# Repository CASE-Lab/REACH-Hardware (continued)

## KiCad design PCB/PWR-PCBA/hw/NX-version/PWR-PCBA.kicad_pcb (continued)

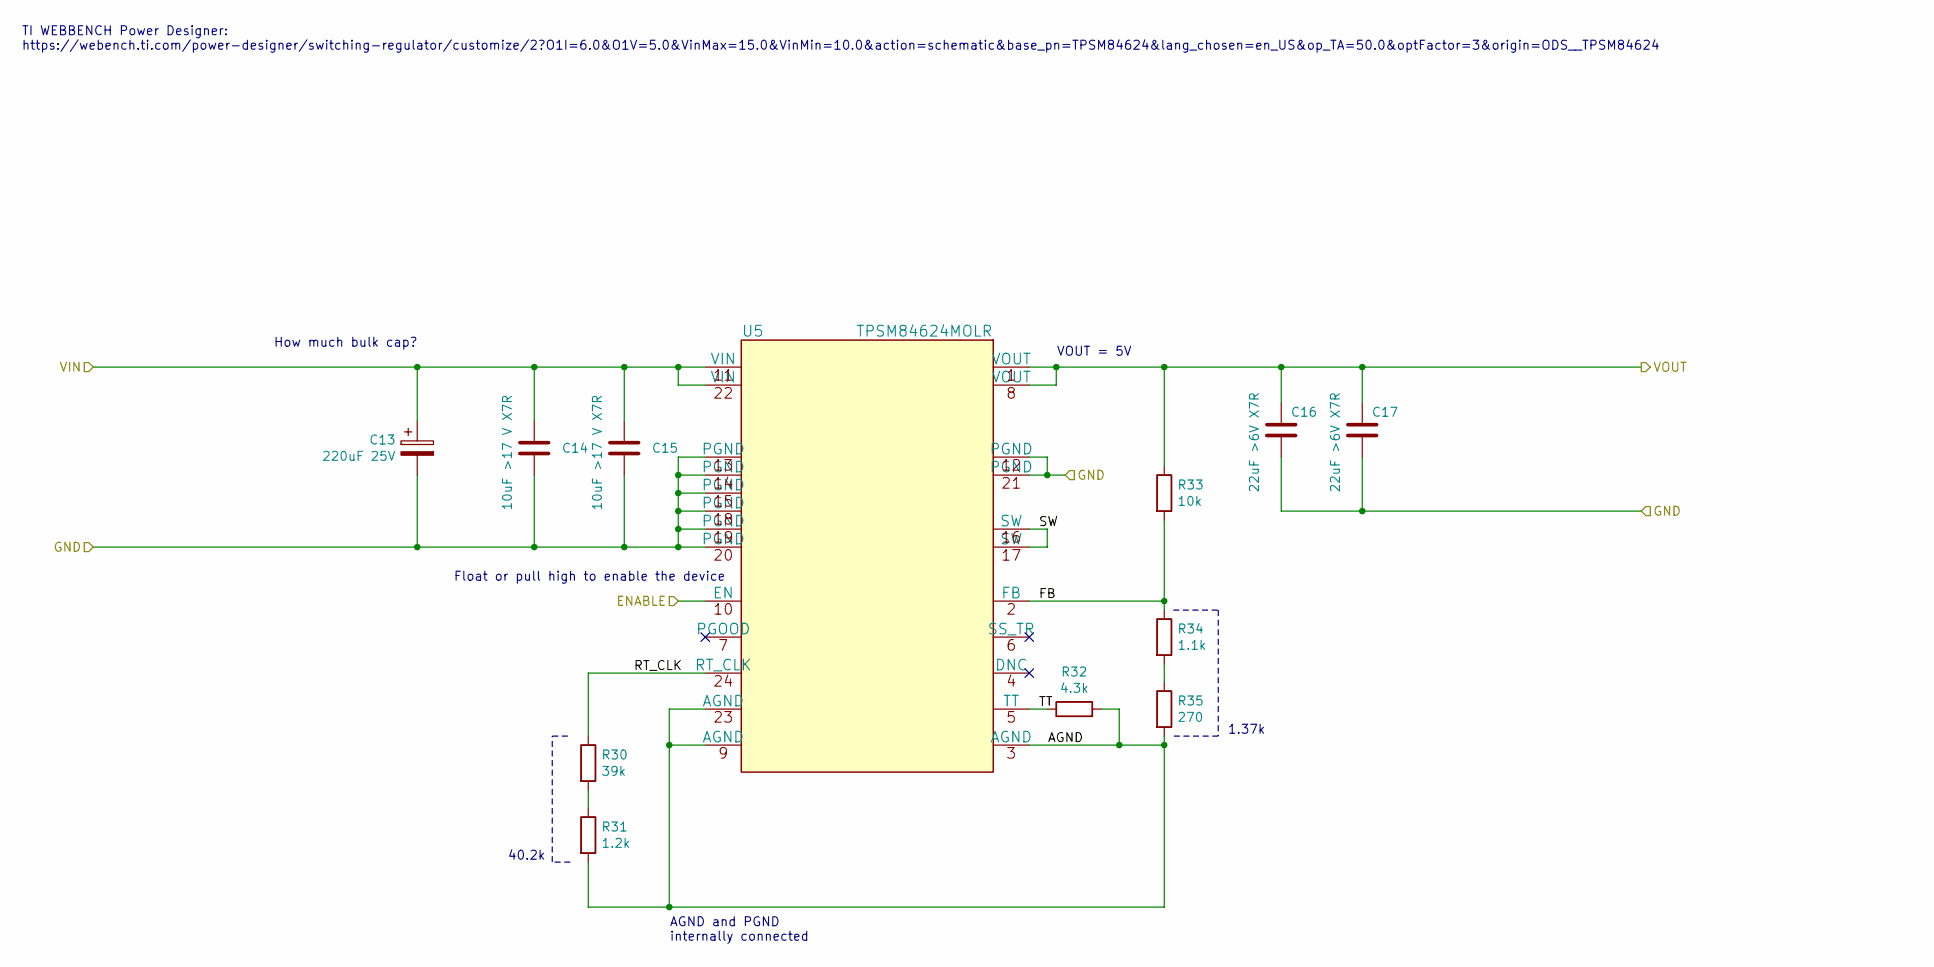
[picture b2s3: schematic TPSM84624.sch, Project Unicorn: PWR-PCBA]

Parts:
C13: 220uF 25V; CP_Radial_D8.0mm_P3.50mm; MPN ESE227M025AG3AA
C14, C15: 10uF >17 V X7R; C_0805_2012Metric; MPN TMK212BBJ106MG-T
C16, C17: 22uF >6V X7R; C_0805_2012Metric; MPN C0805C226M9PACTU
R30: 39k; R_0603_1608Metric
R31: 1.2k; R_0603_1608Metric
R32: 4.3k; R_0603_1608Metric
R33: 10k; R_0603_1608Metric
R34: 1.1k; R_0603_1608Metric
R35: 270; R_0603_1608Metric
U5: TPSM84624MOLR; MPN TPSM84624MOLR

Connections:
+5V: C16.1, C17.1, R33.1, U5.1 (VOUT), U5.8 (VOUT); also elsewhere on the board
+12V: C13.1, C14.1, C15.1, U5.11 (VIN), U5.22 (VIN); also elsewhere on the board
/5V DC/DC TPSM84624 /AGND: R31.2, R32.2, R35.2, U5.3 (AGND), U5.9 (AGND), U5.23 (AGND)
/5V DC/DC TPSM84624 /ENABLE: U5.10 (EN); also elsewhere on the board
/5V DC/DC TPSM84624 /FB: R33.2, R34.1, U5.2 (FB)
/5V DC/DC TPSM84624 /RT_CLK: R30.1, U5.24 (RT_CLK)
/5V DC/DC TPSM84624 /SW: U5.16 (SW), U5.17 (SW)
/5V DC/DC TPSM84624 /TT: R32.1, U5.5 (TT)
GND: C13.2, C14.2, C15.2, C16.2, C17.2, U5.12 (PGND), U5.13 (PGND), U5.14 (PGND), U5.15 (PGND), U5.18 (PGND), U5.19 (PGND), U5.20 (PGND), U5.21 (PGND); also elsewhere on the board
unnamed: R30.2, R31.1
unnamed: R34.2, R35.1

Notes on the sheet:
TI WEBBENCH Power Designer: https://webench.ti.com/power-designer/switching-regulator/customize/2?O1I=6.0&O1V=5.0&VinMax=15.0&VinMin=10.0&action=schematic&base_pn=TPSM84624&lang_chosen=en_US&op_TA=50.0&optFactor=3&origin=ODS__TPSM84624
1.37k
VOUT = 5V
AGND and PGND internally connected
40.2k
How much bulk cap?
Float or pull high to enable the device

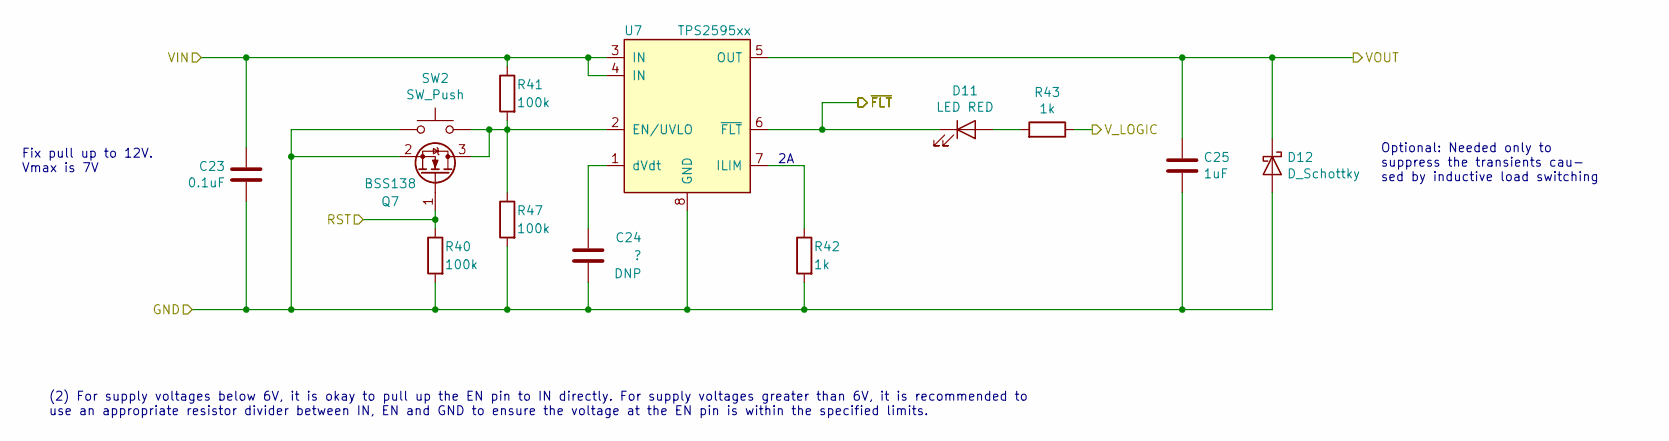
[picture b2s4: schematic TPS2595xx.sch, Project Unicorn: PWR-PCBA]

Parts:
C23: 0.1uF; C_0603_1608Metric
C24: ?; C_0603_1608Metric
C25: 1uF; C_0603_1608Metric
D11: LED RED; LED_0603_1608Metric
D12: D_Schottky; D_SOD-123; MPN 1N5819HW
Q7: BSS138; SOT-23
R40, R41, R47: 100k; R_0603_1608Metric
R42, R43: 1k; R_0603_1608Metric
SW2: SW_Push; KMR621NGLFS; MPN KMR621NGLFS
U7: TPS2595xx; WSON-8-1EP_2x2mm_P0.5mm_EP0.9x1.6mm_ThermalVias; MPN TPS259570DSGR

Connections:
+3V3: R43.1; also elsewhere on the board
+12V: C23.1, R41.1, U7.3 (IN), U7.4 (IN); also elsewhere on the board
/12V_FUSED: C25.1, D12.1 (K), U7.5 (OUT); also elsewhere on the board
/eF_12V_RST: Q7.1 (G), R40.1; also elsewhere on the board
/eF_12V_~FLT: D11.1 (K), U7.6 (~FLT); also elsewhere on the board
GND: C23.2, C24.2, C25.2, D12.2 (A), Q7.2 (S), R40.2, R42.2, R47.2, SW2.1, U7.8 (GND); also elsewhere on the board
unnamed: C24.1, U7.1 (dVdt)
unnamed: D11.2 (A), R43.2
unnamed: Q7.3 (D), R41.2, R47.1, SW2.2, U7.2 (EN/UVLO)
unnamed: R42.1, U7.7 (ILIM)

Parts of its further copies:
C18: 0.1uF; C_0603_1608Metric
C19: ?; C_0603_1608Metric
C20: 1uF; C_0603_1608Metric
D9: LED RED; LED_0603_1608Metric
D10: D_Schottky; D_SOD-123; MPN 1N5819HW
Q6: BSS138; SOT-23
R36, R37, R46: 100k; R_0603_1608Metric
R38, R39: 1k; R_0603_1608Metric
SW1: SW_Push; KMR621NGLFS; MPN KMR621NGLFS
U6: TPS2595xx; WSON-8-1EP_2x2mm_P0.5mm_EP0.9x1.6mm_ThermalVias; MPN TPS259570DSGR

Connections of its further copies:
+3V3: R39.1; also elsewhere on the board
+5V: C18.1, R37.1, U6.3 (IN), U6.4 (IN); also elsewhere on the board
/5V_FUSED: C20.1, D10.1 (K), U6.5 (OUT); also elsewhere on the board
/eF_5V_RST: Q6.1 (G), R36.1; also elsewhere on the board
/eF_5V_~FLT: D9.1 (K), U6.6 (~FLT); also elsewhere on the board
GND: C18.2, C19.2, C20.2, D10.2 (A), Q6.2 (S), R36.2, R38.2, R46.2, SW1.1, U6.8 (GND); also elsewhere on the board
unnamed: C19.1, U6.1 (dVdt)
unnamed: D9.2 (A), R39.2
unnamed: Q6.3 (D), R37.2, R46.1, SW1.2, U6.2 (EN/UVLO)
unnamed: R38.1, U6.7 (ILIM)

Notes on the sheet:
Optional: Needed only to suppress the transients cau- sed by inductive load switching
Fix pull up to 12V. Vmax is 7V
(2) For supply voltages below 6V, it is okay to pull up the EN pin to IN directly. For supply voltages greater than 6V, it is recommended to use an appropriate resistor divider between IN, EN and GND to ensure the voltage at the EN pin is within the specified limits.

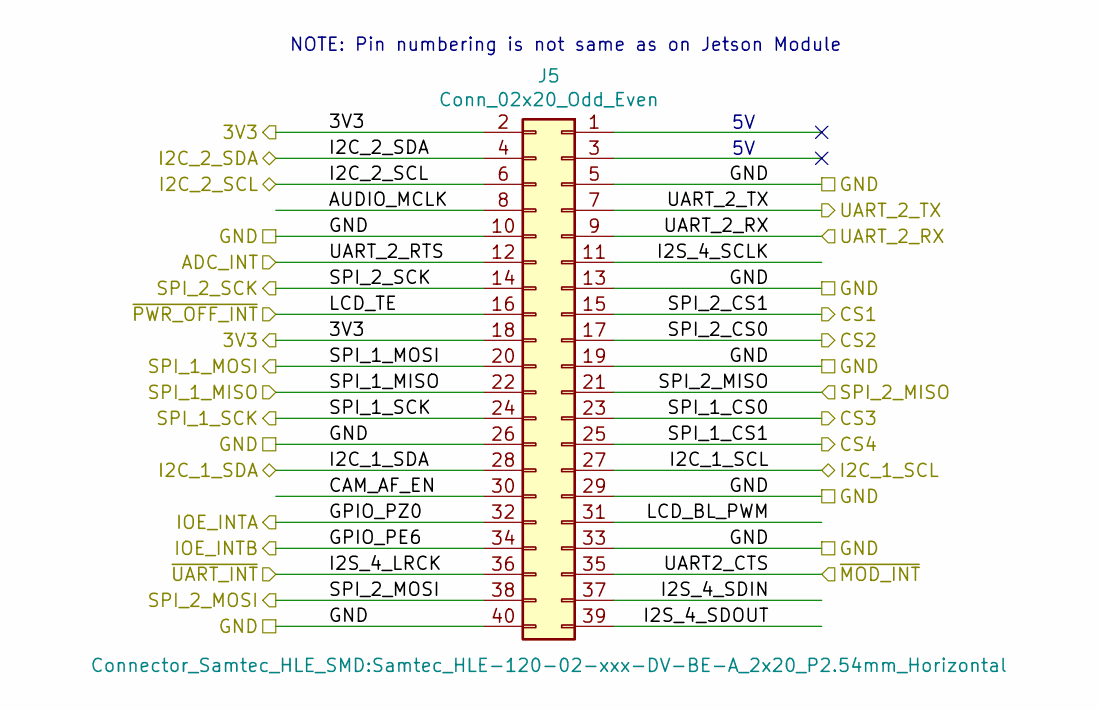
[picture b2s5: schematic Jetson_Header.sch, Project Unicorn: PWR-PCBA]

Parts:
J5: Conn_02x20_Odd_Even; Samtec_HLE-120-02-xxx-DV-BE-A_2x20_P2.54mm_Horizontal; MPN HLE-120-02-F-DV-BE-A

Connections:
+3V3: J5.2, J5.18; also elsewhere on the board
/ADC_INT: J5.12; also elsewhere on the board
/I2C_INT_SCL: J5.6; also elsewhere on the board
/I2C_INT_SDA: J5.4; also elsewhere on the board
/Jetson Header/AUDIO_MCLK: J5.8
/Jetson Header/CAM_AF_EN: J5.30
/Jetson Header/I2C_1_SCL: J5.27; also elsewhere on the board
/Jetson Header/I2C_1_SDA: J5.28; also elsewhere on the board
/Jetson Header/I2S_4_SCLK: J5.11
/Jetson Header/I2S_4_SDIN: J5.37
/Jetson Header/I2S_4_SDOUT: J5.39
/Jetson Header/IOE_INTA: J5.32
/Jetson Header/IOE_INTB: J5.34
/Jetson Header/LCD_BL_PWM: J5.31
/Jetson Header/SPI_1_MISO: J5.22; also elsewhere on the board
/Jetson Header/SPI_1_MOSI: J5.20; also elsewhere on the board
/Jetson Header/SPI_1_SCK: J5.24; also elsewhere on the board
/Jetson Header/SPI_2_MISO: J5.21; also elsewhere on the board
/Jetson Header/SPI_2_MOSI: J5.38; also elsewhere on the board
/Jetson Header/SPI_2_SCK: J5.14; also elsewhere on the board
/Jetson Header/UART_2_RX: J5.9; also elsewhere on the board
/Jetson Header/UART_2_TX: J5.7; also elsewhere on the board
/Jetson Header/~MOD_INT: J5.35; also elsewhere on the board
/Jetson Header/~UART_INT: J5.36; also elsewhere on the board
/SPI_2_CS1: J5.15; also elsewhere on the board
/SPI_2_CS2: J5.17; also elsewhere on the board
/SPI_2_CS3: J5.23; also elsewhere on the board
/SPI_2_CS4: J5.25; also elsewhere on the board
/~PWR_OFF_INT: J5.16; also elsewhere on the board
GND: J5.5, J5.10, J5.13, J5.19, J5.26, J5.29, J5.33, J5.40; also elsewhere on the board

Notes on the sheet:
NOTE: Pin numbering is not same as on Jetson Module

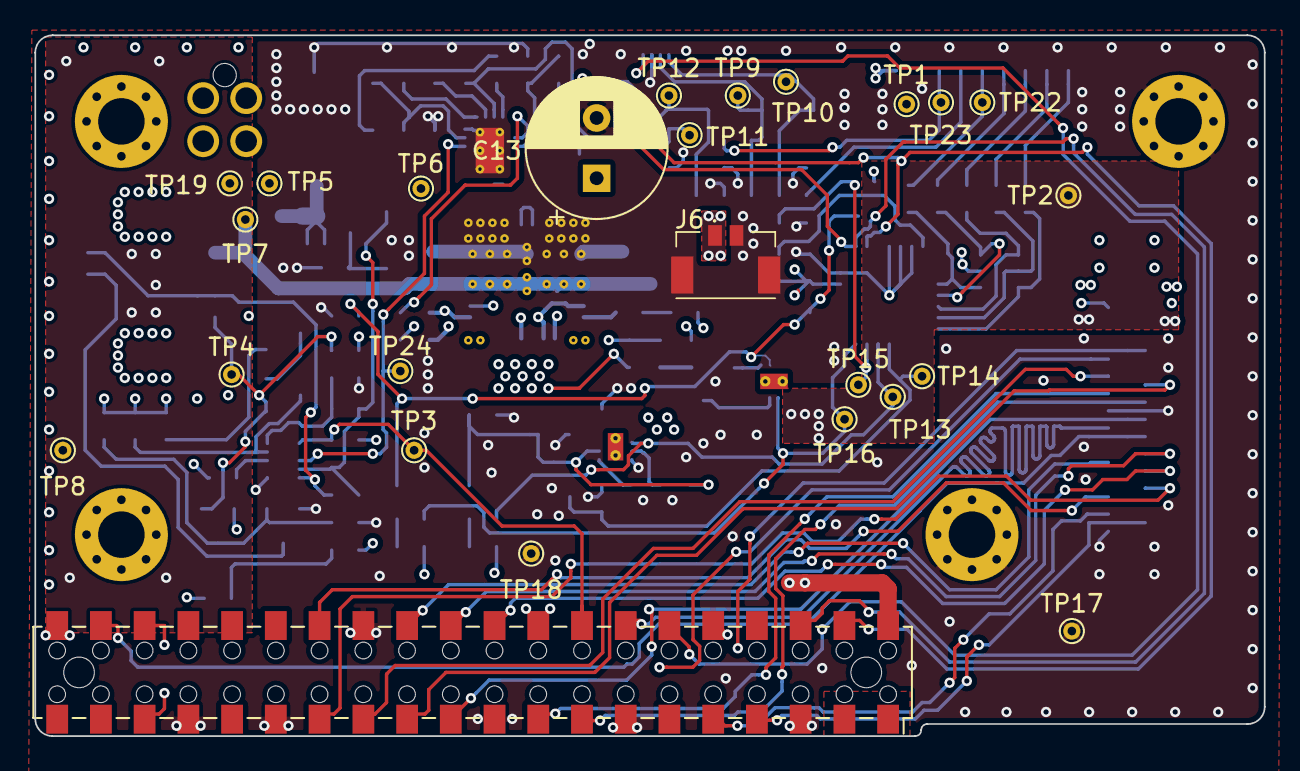
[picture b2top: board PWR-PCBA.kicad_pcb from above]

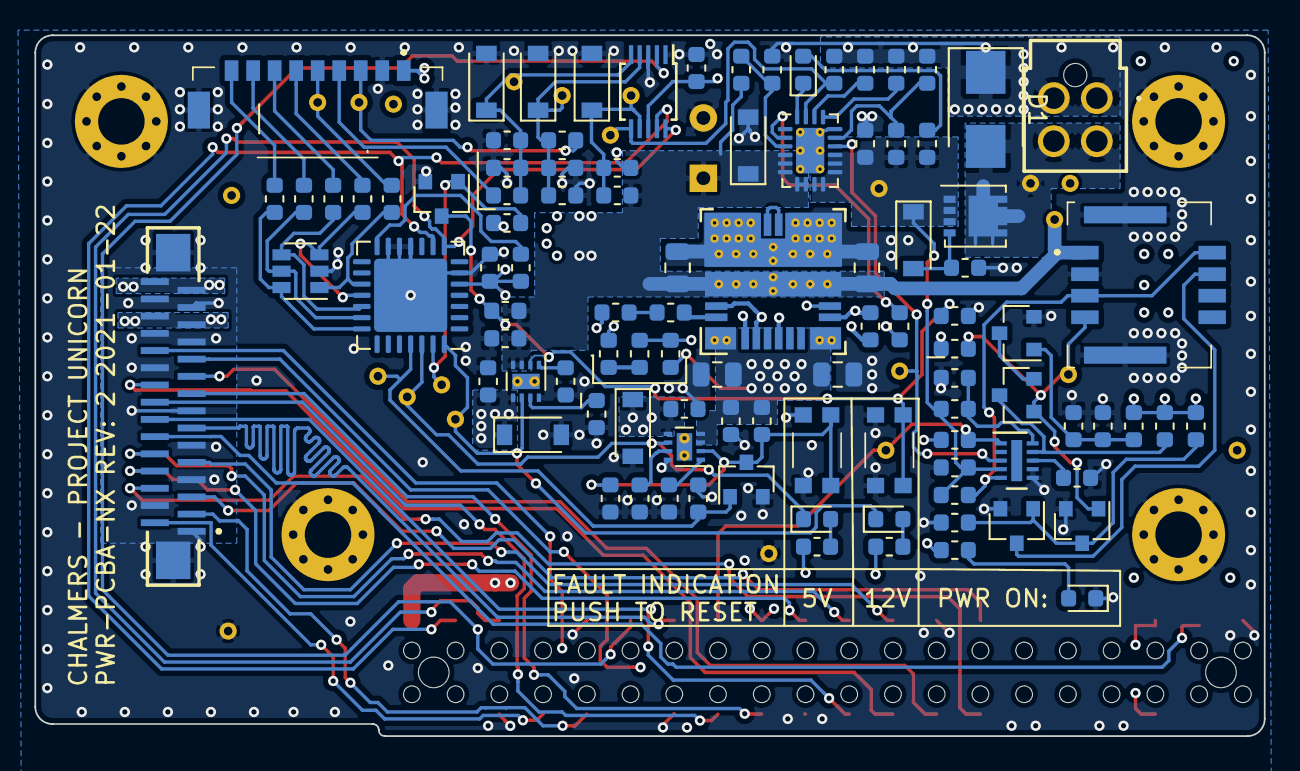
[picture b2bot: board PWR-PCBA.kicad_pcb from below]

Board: 4 copper layers, 71.4 x 40.7 mm, 129 parts (100 on the bottom side), 84 nets.

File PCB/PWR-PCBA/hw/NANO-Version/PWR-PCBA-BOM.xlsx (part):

Project Unicorn: PWR-PCBA BOM |  | Chalmers University of Technology
REV: 2 |  | REV Date: 2020-07-22
Reference | Qty | Value | Distributor | Distributor PN | MPN | Manufacturer | DNP | Comments
Non PCB Items
J1-CABLE | 1 | NanoFit 02x02 cable | Mouser | 538-105308-1204 | 1053081204 | Molex
Nano fit pre-crimped receptable | 2 | 300 mm double ended | Mouser | 538-79758-2140 | 79758-2140 | Molex |  | Buy terminals instead if crimp tool is accessible
J2-CABLE | 1 | MicroLock 02x04 cable | RS | 186-5275 | 505432-0801 | Molex
J4-CABLE | 1 | MicroLock 01x09 cable | Mouser | 538-204532-0901 | 2045320901 | Molex
MicroLock crimp receptable | 17 | Tin plated receptable | RS | 161-5947 | 505431-1000 | Molex |  | Buy crimped leads if no crimp tools is accesible
J5-CABLE | 1 | 30 pin samtec FFC 2" | RS | 197-6642 | FJH-30-D-02.00-4 | Samtec |  | Same side (D)
Kicad CSV Imported Items
C12 C13 | 2 | 220uF 25V | Elfa | 301-51-797 | ESE227M025AG3AA | KEMET
C14 C15 | 2 | 10uF >17 V X7R | RS | 184-3756 | TMK212BBJ106MG-T | Taiyo Yuden
C16 C17 | 2 | 22uF >6V X7R | RS | 691-1177 | C0805C226M9PACTU | Kemet
C2 C6 C1 C7 C8 C3 C10 C18 C23 | 9 | 0.1uF
C4 C5 C20 C25 | 4 | 1uF
C9 C19 C24 | 3 | ? |  |  |  |  | DNP
D1 | 1 | D_TVS | Mouser | 576-TPSMB20CA | TPSMB20CA | Littlefuse
D13 | 1 | LED GREEN
D2 | 1 | 12V | CASE |  | MMSZ5242B-G3-08 | Vishay
D3 D5 D4 | 3 | 5.1V | CASE |  | MMSZ5232B-7-F | Diodes Inc.
D6 | 1 | ESDA6V1-5SC6 | RS | 250-066 | ESDA6V1-5SC6 | ST
D7 D9 D11 | 3 | LED RED
D8 D10 D12 | 3 | D_Schottky | Mouser | 621-1N5819HW-F | 1N5819HW | Diodes Incorporated
H1 H3 H2 H4 | 4 | MountingHole_Pad
J1 | 1 | NanoFit 02x02 | Mouser | 538-105310-1204 | 105310-1204 | Molex
J2 | 1 | Micro Lock 02x04 | RS | 186-5193 | 5054330871 | Molex |  | Connetor for power on/off and LED indication
J3 | 1 | ZF5S-30-03-T-WT | Mouser | 200-ZF5S3003TWTTR | ZF5S-30-03-T-WT-TR | Samtec |  | To FP-PCBA
J4 | 1 | Micro Lock 01x09 | Elfa | 301-76-000 | 205957-0971 | Molex
J5 | 1 | Conn_02x20_Odd_Even | Mouser | 200-HLE12002FDVBEA | HLE-120-02-F-DV-BE-A | Samtec
Q1 | 1 | DMP3013SFV | Mouser | 621-DMP3013SFV-7 | DMP3013SFV-7 | Diodes Incorporated
Q2 Q4 Q5 Q3 Q6 Q7 | 6 | BSS138
R11 R23 | 2 | 1.6M
R13 R17 R15 | 3 | 27k
R2 | 1 | 1M
R22 R21 R20 R19 R18 | 5 | 160
R25 | 1 | 18k
R26 R30 | 2 | 39k
R27 | 1 | 2k
R28 | 1 | 270k
R29 | 1 | 30k
R31 | 1 | 1.2k
R32 | 1 | 4.3k
R33 | 1 | 10k
R34 | 1 | 1.1k
R35 | 1 | 270
R45 R38 R39 R42 R43 | 5 | 1k
R5 R3 R12 R4 R1 R10 R9 R16 R14 R6 R44 R24 R36 R37 R40 R41 | 16 | 100k
R7 | 1 | 0
R8 | 1 | ? |  |  |  |  | DNP
SW1 SW2 | 2 | SW_Push | CASE |  | KMR621NGLFS | C&K Components
TP1 TP2 TP3 TP4 TP21 TP20 TP19 TP18 TP17 TP16 TP15 TP14 TP13 TP12 TP11 TP10 TP9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 | 24 | TestPoint
U1 | 1 | MCP23017_ML | RS | 687-8773 | MCP23017-E/ML | Microchip
U2 | 1 | LTC2955xDDB-1 | RS | 884-6927 | LTC2955IDDB-1#TRMPBF | LT
U3 | 1 | ADS1015BQDGSRQ1 | Mouser | 595-ADS1015BQDGSRQ1 | ADS1015BQDGSRQ1 | TI
U4 | 1 | TPS25940x-Q1 | Mouser | 595-TPS25940LQRVCRQ1 | TPS25940LQRVCRQ1 | TI |  | Latching and automotive variant
U6 U7 | 2 | TPS2595xx | Mouser | 595-TPS259570DSGR | TPS259570DSGR | TI
0 | 0 | 0 | 0 | 0 | 0 | 0 | 0 | 0
0 | 0 | 0 | 0 | 0 | 0 | 0 | 0 | 0
0 | 0 | 0 | 0 | 0 | 0 | 0 | 0 | 0
0 | 0 | 0 | 0 | 0 | 0 | 0 | 0 | 0
0 | 0 | 0 | 0 | 0 | 0 | 0 | 0 | 0
0 | 0 | 0 | 0 | 0 | 0 | 0 | 0 | 0
0 | 0 | 0 | 0 | 0 | 0 | 0 | 0 | 0
0 | 0 | 0 | 0 | 0 | 0 | 0 | 0 | 0
0 | 0 | 0 | 0 | 0 | 0 | 0 | 0 | 0
0 | 0 | 0 | 0 | 0 | 0 | 0 | 0 | 0
0 | 0 | 0 | 0 | 0 | 0 | 0 | 0 | 0
0 | 0 | 0 | 0 | 0 | 0 | 0 | 0 | 0
0 | 0 | 0 | 0 | 0 | 0 | 0 | 0 | 0
0 | 0 | 0 | 0 | 0 | 0 | 0 | 0 | 0
0 | 0 | 0 | 0 | 0 | 0 | 0 | 0 | 0
0 | 0 | 0 | 0 | 0 | 0 | 0 | 0 | 0
0 | 0 | 0 | 0 | 0 | 0 | 0 | 0 | 0
0 | 0 | 0 | 0 | 0 | 0 | 0 | 0 | 0
0 | 0 | 0 | 0 | 0 | 0 | 0 | 0 | 0
0 | 0 | 0 | 0 | 0 | 0 | 0 | 0 | 0
0 | 0 | 0 | 0 | 0 | 0 | 0 | 0 | 0
0 | 0 | 0 | 0 | 0 | 0 | 0 | 0 | 0
0 | 0 | 0 | 0 | 0 | 0 | 0 | 0 | 0
0 | 0 | 0 | 0 | 0 | 0 | 0 | 0 | 0
0 | 0 | 0 | 0 | 0 | 0 | 0 | 0 | 0
0 | 0 | 0 | 0 | 0 | 0 | 0 | 0 | 0
0 | 0 | 0 | 0 | 0 | 0 | 0 | 0 | 0
0 | 0 | 0 | 0 | 0 | 0 | 0 | 0 | 0
0 | 0 | 0 | 0 | 0 | 0 | 0 | 0 | 0
0 | 0 | 0 | 0 | 0 | 0 | 0 | 0 | 0
0 | 0 | 0 | 0 | 0 | 0 | 0 | 0 | 0
0 | 0 | 0 | 0 | 0 | 0 | 0 | 0 | 0
0 | 0 | 0 | 0 | 0 | 0 | 0 | 0 | 0
0 | 0 | 0 | 0 | 0 | 0 | 0 | 0 | 0
0 | 0 | 0 | 0 | 0 | 0 | 0 | 0 | 0
0 | 0 | 0 | 0 | 0 | 0 | 0 | 0 | 0
0 | 0 | 0 | 0 | 0 | 0 | 0 | 0 | 0
0 | 0 | 0 | 0 | 0 | 0 | 0 | 0 | 0
0 | 0 | 0 | 0 | 0 | 0 | 0 | 0 | 0
0 | 0 | 0 | 0 | 0 | 0 | 0 | 0 | 0
0 | 0 | 0 | 0 | 0 | 0 | 0 | 0 | 0
0 | 0 | 0 | 0 | 0 | 0 | 0 | 0 | 0
0 | 0 | 0 | 0 | 0 | 0 | 0 | 0 | 0
0 | 0 | 0 | 0 | 0 | 0 | 0 | 0 | 0
0 | 0 | 0 | 0 | 0 | 0 | 0 | 0 | 0
0 | 0 | 0 | 0 | 0 | 0 | 0 | 0 | 0
0 | 0 | 0 | 0 | 0 | 0 | 0 | 0 | 0
0 | 0 | 0 | 0 | 0 | 0 | 0 | 0 | 0
0 | 0 | 0 | 0 | 0 | 0 | 0 | 0 | 0
0 | 0 | 0 | 0 | 0 | 0 | 0 | 0 | 0
0 | 0 | 0 | 0 | 0 | 0 | 0 | 0 | 0
0 | 0 | 0 | 0 | 0 | 0 | 0 | 0 | 0
0 | 0 | 0 | 0 | 0 | 0 | 0 | 0 | 0
0 | 0 | 0 | 0 | 0 | 0 | 0 | 0 | 0
0 | 0 | 0 | 0 | 0 | 0 | 0 | 0 | 0
0 | 0 | 0 | 0 | 0 | 0 | 0 | 0 | 0
0 | 0 | 0 | 0 | 0 | 0 | 0 | 0 | 0
0 | 0 | 0 | 0 | 0 | 0 | 0 | 0 | 0
0 | 0 | 0 | 0 | 0 | 0 | 0 | 0 | 0
0 | 0 | 0 | 0 | 0 | 0 | 0 | 0 | 0
0 | 0 | 0 | 0 | 0 | 0 | 0 | 0 | 0
0 | 0 | 0 | 0 | 0 | 0 | 0 | 0 | 0
0 | 0 | 0 | 0 | 0 | 0 | 0 | 0 | 0
0 | 0 | 0 | 0 | 0 | 0 | 0 | 0 | 0
0 | 0 | 0 | 0 | 0 | 0 | 0 | 0 | 0
0 | 0 | 0 | 0 | 0 | 0 | 0 | 0 | 0
0 | 0 | 0 | 0 | 0 | 0 | 0 | 0 | 0
0 | 0 | 0 | 0 | 0 | 0 | 0 | 0 | 0
0 | 0 | 0 | 0 | 0 | 0 | 0 | 0 | 0
0 | 0 | 0 | 0 | 0 | 0 | 0 | 0 | 0
0 | 0 | 0 | 0 | 0 | 0 | 0 | 0 | 0
0 | 0 | 0 | 0 | 0 | 0 | 0 | 0 | 0
0 | 0 | 0 | 0 | 0 | 0 | 0 | 0 | 0
0 | 0 | 0 | 0 | 0 | 0 | 0 | 0 | 0
0 | 0 | 0 | 0 | 0 | 0 | 0 | 0 | 0
0 | 0 | 0 | 0 | 0 | 0 | 0 | 0 | 0
0 | 0 | 0 | 0 | 0 | 0 | 0 | 0 | 0
0 | 0 | 0 | 0 | 0 | 0 | 0 | 0 | 0
0 | 0 | 0 | 0 | 0 | 0 | 0 | 0 | 0
0 | 0 | 0 | 0 | 0 | 0 | 0 | 0 | 0
0 | 0 | 0 | 0 | 0 | 0 | 0 | 0 | 0
0 | 0 | 0 | 0 | 0 | 0 | 0 | 0 | 0
0 | 0 | 0 | 0 | 0 | 0 | 0 | 0 | 0
0 | 0 | 0 | 0 | 0 | 0 | 0 | 0 | 0
0 | 0 | 0 | 0 | 0 | 0 | 0 | 0 | 0
0 | 0 | 0 | 0 | 0 | 0 | 0 | 0 | 0
0 | 0 | 0 | 0 | 0 | 0 | 0 | 0 | 0
0 | 0 | 0 | 0 | 0 | 0 | 0 | 0 | 0
0 | 0 | 0 | 0 | 0 | 0 | 0 | 0 | 0
0 | 0 | 0 | 0 | 0 | 0 | 0 | 0 | 0
0 | 0 | 0 | 0 | 0 | 0 | 0 | 0 | 0
0 | 0 | 0 | 0 | 0 | 0 | 0 | 0 | 0
0 | 0 | 0 | 0 | 0 | 0 | 0 | 0 | 0
0 | 0 | 0 | 0 | 0 | 0 | 0 | 0 | 0
0 | 0 | 0 | 0 | 0 | 0 | 0 | 0 | 0
0 | 0 | 0 | 0 | 0 | 0 | 0 | 0 | 0
0 | 0 | 0 | 0 | 0 | 0 | 0 | 0 | 0
0 | 0 | 0 | 0 | 0 | 0 | 0 | 0 | 0
0 | 0 | 0 | 0 | 0 | 0 | 0 | 0 | 0
0 | 0 | 0 | 0 | 0 | 0 | 0 | 0 | 0
0 | 0 | 0 | 0 | 0 | 0 | 0 | 0 | 0
0 | 0 | 0 | 0 | 0 | 0 | 0 | 0 | 0
0 | 0 | 0 | 0 | 0 | 0 | 0 | 0 | 0
0 | 0 | 0 | 0 | 0 | 0 | 0 | 0 | 0
0 | 0 | 0 | 0 | 0 | 0 | 0 | 0 | 0
0 | 0 | 0 | 0 | 0 | 0 | 0 | 0 | 0
0 | 0 | 0 | 0 | 0 | 0 | 0 | 0 | 0
0 | 0 | 0 | 0 | 0 | 0 | 0 | 0 | 0
0 | 0 | 0 | 0 | 0 | 0 | 0 | 0 | 0
0 | 0 | 0 | 0 | 0 | 0 | 0 | 0 | 0
0 | 0 | 0 | 0 | 0 | 0 | 0 | 0 | 0
0 | 0 | 0 | 0 | 0 | 0 | 0 | 0 | 0
0 | 0 | 0 | 0 | 0 | 0 | 0 | 0 | 0
0 | 0 | 0 | 0 | 0 | 0 | 0 | 0 | 0
0 | 0 | 0 | 0 | 0 | 0 | 0 | 0 | 0
0 | 0 | 0 | 0 | 0 | 0 | 0 | 0 | 0
0 | 0 | 0 | 0 | 0 | 0 | 0 | 0 | 0
0 | 0 | 0 | 0 | 0 | 0 | 0 | 0 | 0
0 | 0 | 0 | 0 | 0 | 0 | 0 | 0 | 0
0 | 0 | 0 | 0 | 0 | 0 | 0 | 0 | 0
0 | 0 | 0 | 0 | 0 | 0 | 0 | 0 | 0
0 | 0 | 0 | 0 | 0 | 0 | 0 | 0 | 0
0 | 0 | 0 | 0 | 0 | 0 | 0 | 0 | 0
0 | 0 | 0 | 0 | 0 | 0 | 0 | 0 | 0
0 | 0 | 0 | 0 | 0 | 0 | 0 | 0 | 0
0 | 0 | 0 | 0 | 0 | 0 | 0 | 0 | 0
0 | 0 | 0 | 0 | 0 | 0 | 0 | 0 | 0
0 | 0 | 0 | 0 | 0 | 0 | 0 | 0 | 0
0 | 0 | 0 | 0 | 0 | 0 | 0 | 0 | 0
0 | 0 | 0 | 0 | 0 | 0 | 0 | 0 | 0
0 | 0 | 0 | 0 | 0 | 0 | 0 | 0 | 0
0 | 0 | 0 | 0 | 0 | 0 | 0 | 0 | 0
0 | 0 | 0 | 0 | 0 | 0 | 0 | 0 | 0
0 | 0 | 0 | 0 | 0 | 0 | 0 | 0 | 0
0 | 0 | 0 | 0 | 0 | 0 | 0 | 0 | 0
0 | 0 | 0 | 0 | 0 | 0 | 0 | 0 | 0
0 | 0 | 0 | 0 | 0 | 0 | 0 | 0 | 0
0 | 0 | 0 | 0 | 0 | 0 | 0 | 0 | 0
0 | 0 | 0 | 0 | 0 | 0 | 0 | 0 | 0
0 | 0 | 0 | 0 | 0 | 0 | 0 | 0 | 0
0 | 0 | 0 | 0 | 0 | 0 | 0 | 0 | 0
0 | 0 | 0 | 0 | 0 | 0 | 0 | 0 | 0
0 | 0 | 0 | 0 | 0 | 0 | 0 | 0 | 0
0 | 0 | 0 | 0 | 0 | 0 | 0 | 0 | 0
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
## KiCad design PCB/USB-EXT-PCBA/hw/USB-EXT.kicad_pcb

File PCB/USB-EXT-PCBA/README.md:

# USB-EXT-PCBA

USB interconnection to bring down upper USB connections to

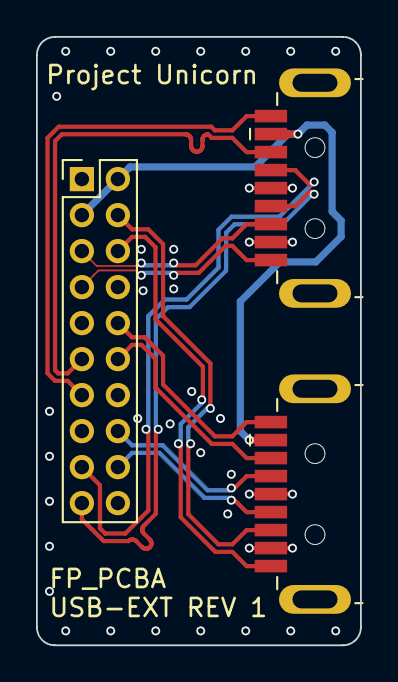
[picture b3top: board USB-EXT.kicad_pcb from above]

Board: 4 copper layers, 18.0 x 33.8 mm, 3 parts (0 on the bottom side), 14 nets.

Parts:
J1: 2x USB 3.0 Header; PinHeader_2x10_P2.00mm_Vertical
J2, J3: USB3_A; USB3_A_Plug_AMPHENOL_GSB316441CEU

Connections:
/IntA_P1_D+: J1.18, J2.3
/IntA_P1_D-: J1.16, J2.2
/IntA_P1_SSRX+: J1.6, J2.5
/IntA_P1_SSRX-: J1.4, J2.6
/IntA_P1_SSTX+: J1.12, J2.8
/IntA_P1_SSTX-: J1.10, J2.9
/IntA_P2_D+: J1.19, J3.3
/IntA_P2_D-: J1.17, J3.2
/IntA_P2_SSRX+: J1.7, J3.5
/IntA_P2_SSRX-: J1.5, J3.6
/IntA_P2_SSTX+: J1.13, J3.9
/IntA_P2_SSTX-: J1.11, J3.8
GND: J1.8, J1.9, J1.14, J1.15, J2.4, J2.7, J2.10, J3.4, J3.7, J3.10
VBUS: J1.2, J1.3, J2.1, J3.1

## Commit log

2021-09-06 initial commit CAD files
2021-09-12 added images of the standard version
2021-09-12 Create LICENSE
2021-09-12 added more images
2024-02-23 added 10Gbit version, not finished
2024-02-26 10GbE connector now on front panel
2024-03-06 added new cable fastener for 10Gbit version
2024-03-08 added CAM for front panel 10Gbit version
